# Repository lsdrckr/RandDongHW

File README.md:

# Stage chez Rang Dong

## Introduction

Dans le cadre de mon stage au Vietnam au Posts and Telecommunications Institute of Technologies, j'ai eu l'occasion de réaliser un projet avec une de leurs entreprise partenaire : Rand Dong. Cette entreprise est spécialisé dans la conception et la vente de matériel pour la domotique (smart home, smart cities...) tels que des lampes connectés, des hubs de capteurs (température, pression...) ou encore des caméras connectés. J'ai eu l'occasion de rejoindre 4 équipes :
- software : design d'application mobiles
- firmware : programmation de systèmes embarqués
- cloud : stockage dans des databases
- hardware : design de circuit imprimé
Mon choix s'est tourné vers le hardware, domaine dans lequel j'ai pu approfondir mes connaissances, et ce principalement d'un point de vue technique, grâce à l'équipe de Rang Dong qui m'a épaulé durant l'entièreté de mon stage.

## Projet

Le projet qui m'a été confié fût de réalisé un "Touch switch". Il s'agit d'interrupteurs tactiles permettant de contrôler, dans le cas de mon projet, 4 lampes. Voici ci-dessous une photo d'un produit commercialisé par Rand Dong sur lequel je vais me baser.

<center>
  <table>
    <tr>
      <td align="center">
        
        <br>
        <em>Touch Switch de chez Rang Dong</em>
      </td>
    </tr>
  </table>
</center>

A l'aide d'un contact avec le doigt sur l'un des ronds bleus, on allume une lampe à proximité. Ce principe à l'air simple car il est couramment utilisé et il nous accompagne au quotidien. Cependant, nous allons voir comment un tel projet est réalisé du début à la fin. Chez Rang Dong, ce genre d'objets est réalisé en 3 parties :
- une carte servant à l'alimentation (conversion AC/DC, relais...)
- une carte destiné au contrôle (microprocesseur...)
- le design de l'objet en lui-même, dans lequel sont camouflés les précédentes cartes
Dans un premier temps, j'ai conçu la carte servant à l'alimentation.

## Alimentation

### Choix des technologies

Le choix de l'alimentation est très importante pour tout projet, mais il l'est d'autant plus pour un projet comme celui-ci. En effet, ce dernier est destiné à n'importe quel client et de plus, ce client devra être en contact direct avec l'objet s'il souhaite l'utiliser. C'est pourquoi la sécurité était l'argument numéro un lors de mon choix. 2 propositions se sont vite dégagés au sein de l'équipe :
- alimentation buck
- alimentation flyback
D'un côté, l'alimentation buck permet la conversion à l'aide d'une inductance tandis que le flyback utilise un transformateur. De plus, le flyback permet une isolation galvanique entre la partie AC et la partie DC de la carte. Cependant, l'implémentation du flyback est plus compliqué que celle de l'alimentation buck. Comme dit précédemment, la sécurité de notre système est primordiale. Nous avons donc choisi l'alimentation flyback.

Nous avions besoin de récupérer 2 valeurs de tensions différents :
- une de 5V pour alimenter les relais
- une de 3.3V pour alimenter la carte de contrôle
Deux propositions sont égalements possible, dont voici les schémas équivalents :

<center>
  <table>
    <tr>
      <td align="center">
        
        <br>
        <em>Proposition 1 pour l'alim AC</em>
      </td>
      <td align="center">
        
        <br>
        <em>Proposition 2 pour l'alim AC</em>
      </td>
    </tr>
  </table>
</center>

Le premier choix consiste à utiliser 2 transformateurs ayant deux sorties et donc deux tensions de sortie différentes. Le deuxième, quant à lui, consiste à utiliser un régulateur de tension LDO pour récupérer 3.3V à partie des 5V de sortie du transformateur. Mon choix s’est naturellement posé sur le LDO, moins complexe à mettre en place et moins coûteux.
On mettra à l’entrée du transformateur un bloc snubber, permettant de limiter les pics de tension de l’alimentation AC et donc de protéger le transformateur.

### Choix des composants

Cette partie m’a énormément appris. Elle consiste non seulement à déterminer la valeurs des composants (résistances, capacités…) mais aussi à déterminer la taille des ses derniers en fonction de la puissance dissipée dans les résistances ou de la tension maximum des capacités. Pour les résistances, je me suis basé sur le tableau suivant venant de Fenghua.

<center>
  <table>
    <tr>
      <td align="center">
        
        <br>
        <em>Tableau de taille des résistances</em>
      </td>
    </tr>
  </table>
</center>

Pour les capacités, j’ai suivi le tableau de chez Kemet, qui donne la taille des composants en fonction de leurs valeurs et tension maximale.

<center>
  <table>
    <tr>
      <td align="center">
        
        <br>
        <em>Loi d'Ohm</em>
      </td>
    </tr>
  </table>
</center>

Pour mieux comprendre, voici un exemple rapide. Une résistance R est traversée par un courant I et a à ses bornes une tension V. La puissance qu’elle va dissiper est P = V\*I. En fonction de si l’on connaît seulement I ou V, on peut aussi déduire de la loi d'Ohm que P = V²/R ou P = I²\*R. Prenons dans notre exemple que nous avons déterminé R=1kΩ et Vmax=15V. On a alors P = 0,225W. En nous référant au tableau ci-dessus, on peut alors se permettre de choisir une résistance de taille 1206 ou plus, qui peut dissiper au maximum ¼W = 0,25W. Dans le cas où la puissance dépasse ½W, on peut mettre 2 résistances en parallèles, qui pourront dissiper 2 fois plus de puissance tout en gardant la même valeur. Prenons cette fois-ci Vmax=25V. On a alors P = 0,625W. En mettant deux résistances de 2kΩ en parallèle, on garde une résistance équivalente de 1kΩ et chacune d’entre elles doit seulement dissiper 0,3125W. Dans ce cas, on pourra choisir deux résistances de taille 2512.
Je n’ai pas détaillé le calcul pour chacun des composants, mais voici la méthode que j’ai suivie pour trouver leurs tailles.

### Implémentation sur Kicad

Maintenant que j’ai tous les éléments, je peux commencer à implémenter mon projet sur Kicad. J’ai séparé ce dernier en 4 grandes parties :

<center>
  <table>
    <tr>
      <td align="center">
        
        <br>
        <em>Alimentation AC</em>
      </td>
      <td align="center">
        
        <br>
        <em>Transformateur</em>
      </td>
    </tr>
    <tr>
      <td align="center">
        
        <br>
        <em>Driver flyback</em>
      </td>
      <td align="center">
        
        <br>
        <em>Relais</em>
      </td>
    </tr>
  </table>
</center>

J’ai également ajouté un connecteur 8 pins pour relier cette carte à celle de contrôle auquel seront connectés les sorties des 4 relais, la sortie du régulateur en 3.3V et la masse lui étant associée.
J’ai ensuite assigné chacun des éléments avec leurs empreintes, soit en choisissant les tailles définies précédemment, soit en demandant à mon équipe les datasheets qu’ils ont l’habitude d’utiliser pour les composants “spéciaux” tels que le driver, le transformateur, les relais…

## Bibliographie

[Page git du projet](https://github.com/lsdrckr/RangDongHW.git)

[Taille des résistances](https://www.fenghua.com/pdf/thickfilmchipres/thin_film_chipres.pdf)

[Taille des condensateurs](https://www.mouser.com/datasheet/2/447/KEM_A4005_ESH-3315849.pdf)

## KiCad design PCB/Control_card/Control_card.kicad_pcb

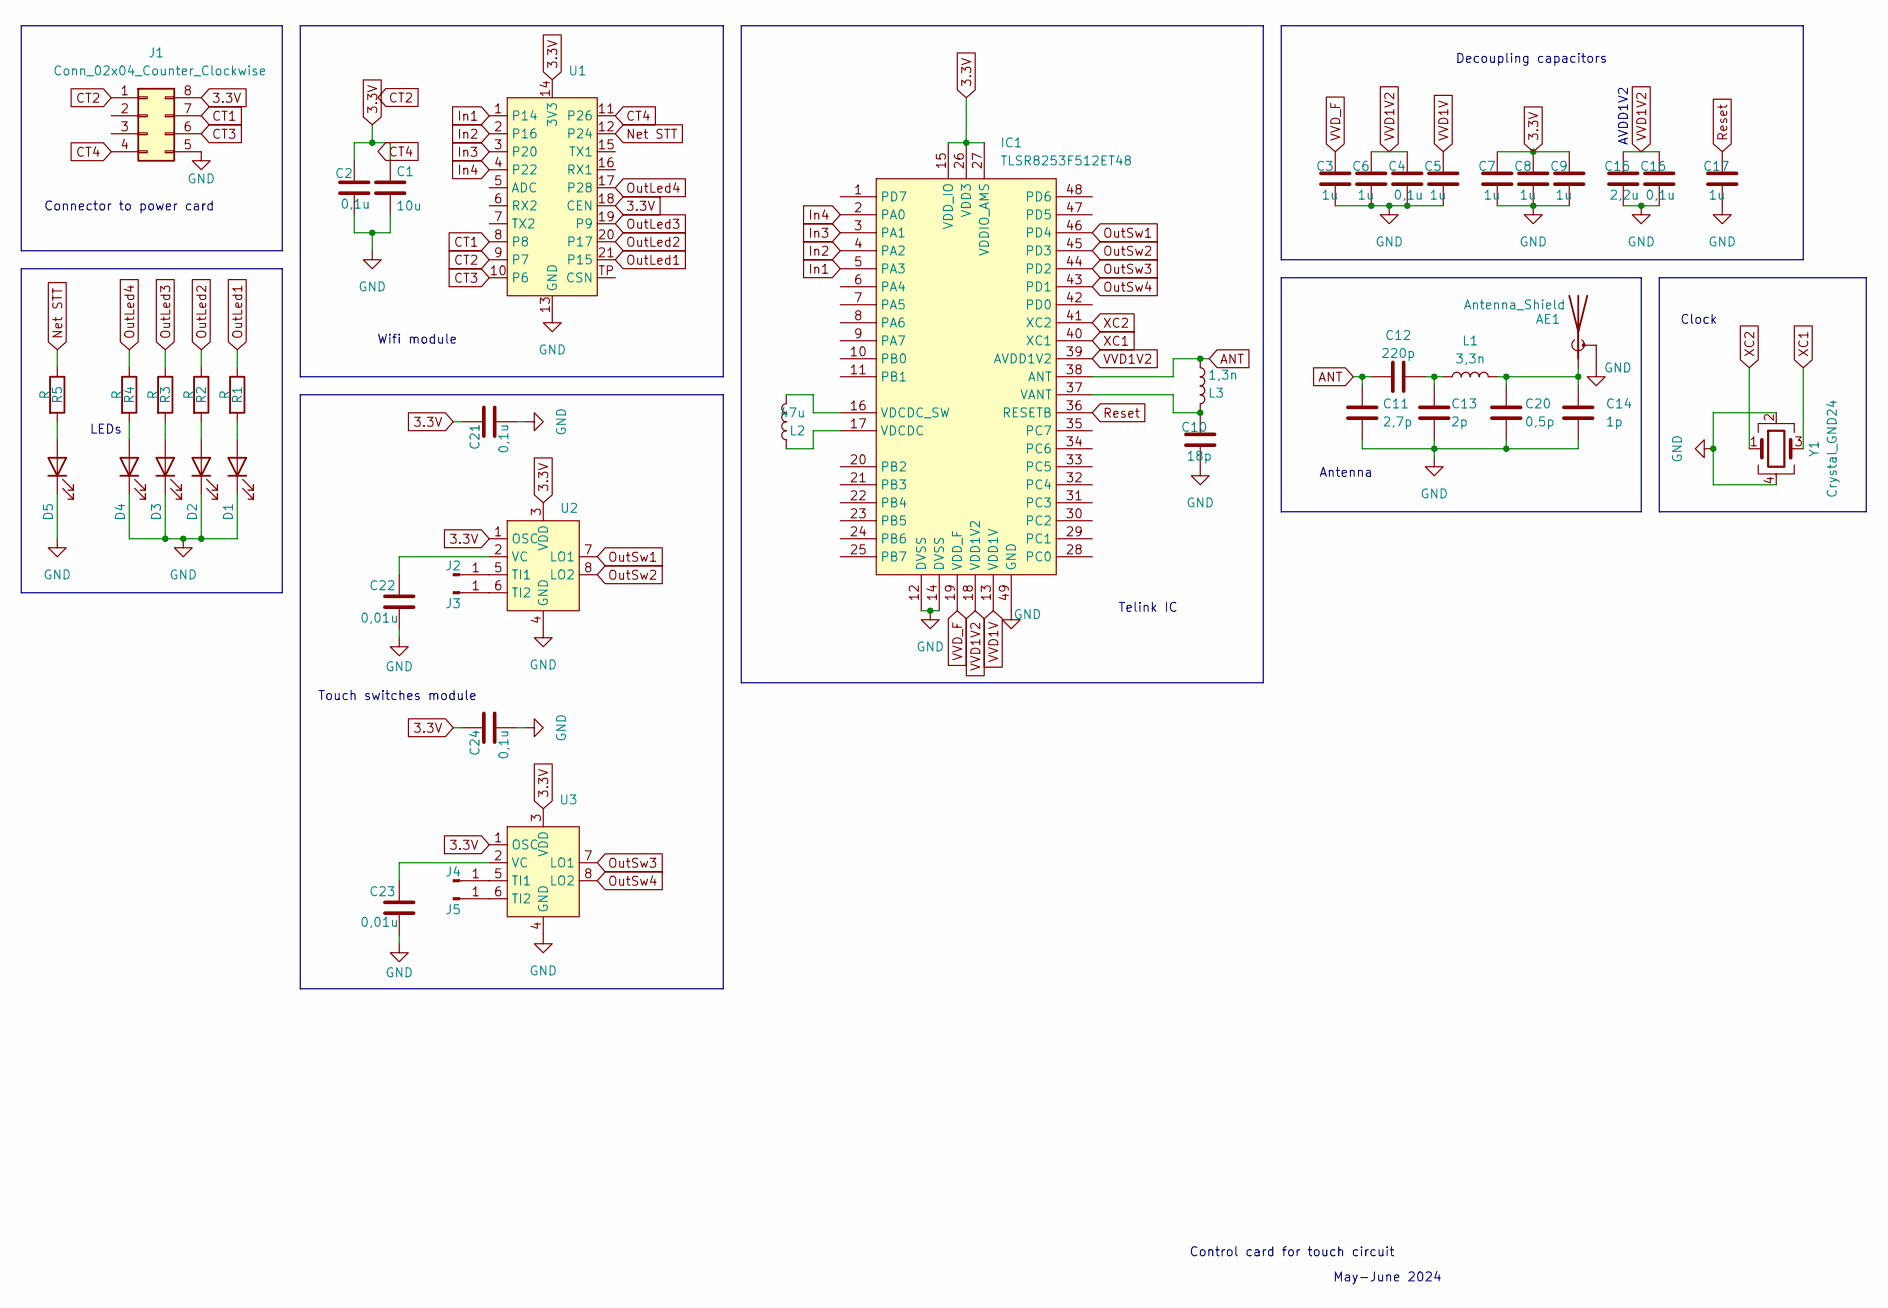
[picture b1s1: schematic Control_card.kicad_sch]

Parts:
AE1: Antenna_Shield; Antenna
C1: 10u; C_0603_1608Metric
C2, C4, C16, C21, C24: 0,1u; C_0603_1608Metric
C3, C5, C6, C7, C8, C9, C17: 1u; C_0603_1608Metric
C10: 18p; C_0603_1608Metric
C11: 2,7p; C_0603_1608Metric
C12: 220p; C_0603_1608Metric
C13: 2p; C_0603_1608Metric
C14: 1p; C_0603_1608Metric
C15: 2,2u; C_0603_1608Metric
C20: 0,5p; C_0603_1608Metric
C22, C23: 0,01u; C_0603_1608Metric
D1, D2, D3, D4, D5: LED; LED_0805_2012Metric
IC1: TLSR8253F512ET48; QFN-48-1EP_7x7mm_P0.5mm_EP5.6x5.6mm_ThermalVias; Mouser Part Number 141-TLSR8253F512ET32
J1: Conn_02x04_Counter_Clockwise; PinMale
J2, J3, J4, J5: Conn_01x01_Pin; TouchSwitch
L1: 3,3n; L_0603_1608Metric
L2: 47u; L_0805_2012Metric
L3: 1,3n; L_0603_1608Metric
R1, R2, R3, R4, R5: R; R_0603_1608Metric
U1: BK7231N
U2, U3: SOP-8_3.9x4.9mm_P1.27mm
Y1: Crystal_GND24; Crystal

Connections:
3.3V: C1.1, C2.1, C7.1, C8.1, C9.1, C21.1, C24.1, IC1.15 (VDD_IO), IC1.26 (VDD3), IC1.27 (VDDIO_AMS), J1.8, U1.14 (3V3), U1.18 (CEN), U2.1 (OSC), U2.3 (VDD), U3.1 (OSC), U3.3 (VDD)
ANT: C11.1, C12.1, IC1.38 (ANT), L3.2
CT1: J1.7, U1.8
CT2: J1.1, U1.9 (P7)
CT3: J1.6, U1.10 (P6)
CT4: J1.4, U1.11 (P26)
GND: AE1.2 (Shield), C1.2, C2.2, C3.2, C4.2, C5.2, C6.2, C7.2, C8.2, C9.2, C10.2, C11.2, C13.2, C14.2, C15.2, C16.2, C17.2, C20.2, C21.2, C22.2, C23.2, C24.2, D1.1 (K), D2.1 (K), D3.1 (K), D4.1 (K), D5.1 (K), IC1.12 (DVSS), IC1.14 (DVSS), IC1.49 (GND), J1.5, U1.13 (GND), U2.4 (GND), U3.4 (GND), Y1.2, Y1.4
In1: IC1.5 (PA3), U1.1 (P14)
In2: IC1.4 (PA2), U1.2 (P16)
In3: IC1.3 (PA1), U1.3 (P20)
In4: IC1.2 (PA0), U1.4 (P22)
Net STT: R5.1, U1.12 (P24)
unnamed: AE1.1 (A), C14.1, C20.1, L1.2
unnamed: C12.2, C13.1, L1.1
unnamed: D1.2 (A), R1.2
unnamed: D2.2 (A), R2.2
unnamed: D3.2 (A), R3.2
unnamed: D4.2 (A), R4.2
unnamed: D5.2 (A), R5.2
unnamed: C10.1, IC1.37 (VANT), L3.1
unnamed: IC1.17 (VDCDC), L2.1
unnamed: IC1.16 (VDCDC_SW), L2.2
unnamed: J2.1, U2.5 (TI1)
unnamed: J3.1, U2.6 (TI2)
unnamed: J4.1, U3.5 (TI1)
unnamed: J5.1, U3.6 (TI2)
unnamed: C22.1, U2.2 (VC)
unnamed: C23.1, U3.2 (VC)
OutLed1: R1.1, U1.21 (P15)
OutLed2: R2.1, U1.20 (P17)
OutLed3: R3.1, U1.19 (P9)
OutLed4: R4.1, U1.17 (P28)
OutSw1: IC1.46 (PD4), U2.7 (LO1)
OutSw2: IC1.45 (PD3), U2.8 (LO2)
OutSw3: IC1.44 (PD2), U3.7 (LO1)
OutSw4: IC1.43 (PD1), U3.8 (LO2)
Reset: C17.1, IC1.36 (RESETB)
VVD1V: C5.1, IC1.13 (VDD1V)
VVD1V2: C4.1, C6.1, C15.1, C16.1, IC1.18 (VDD1V2), IC1.39 (AVDD1V2)
VVD_F: C3.1, IC1.19 (VDD_F)
XC1: IC1.40 (XC1), Y1.3
XC2: IC1.41 (XC2), Y1.1

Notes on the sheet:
Connector to power card
Wifi module
LEDs
Decoupling capacitors
May-June 2024
Control card for touch circuit
Antenna
Telink IC
Touch switches module
Clock
AVDD1V2

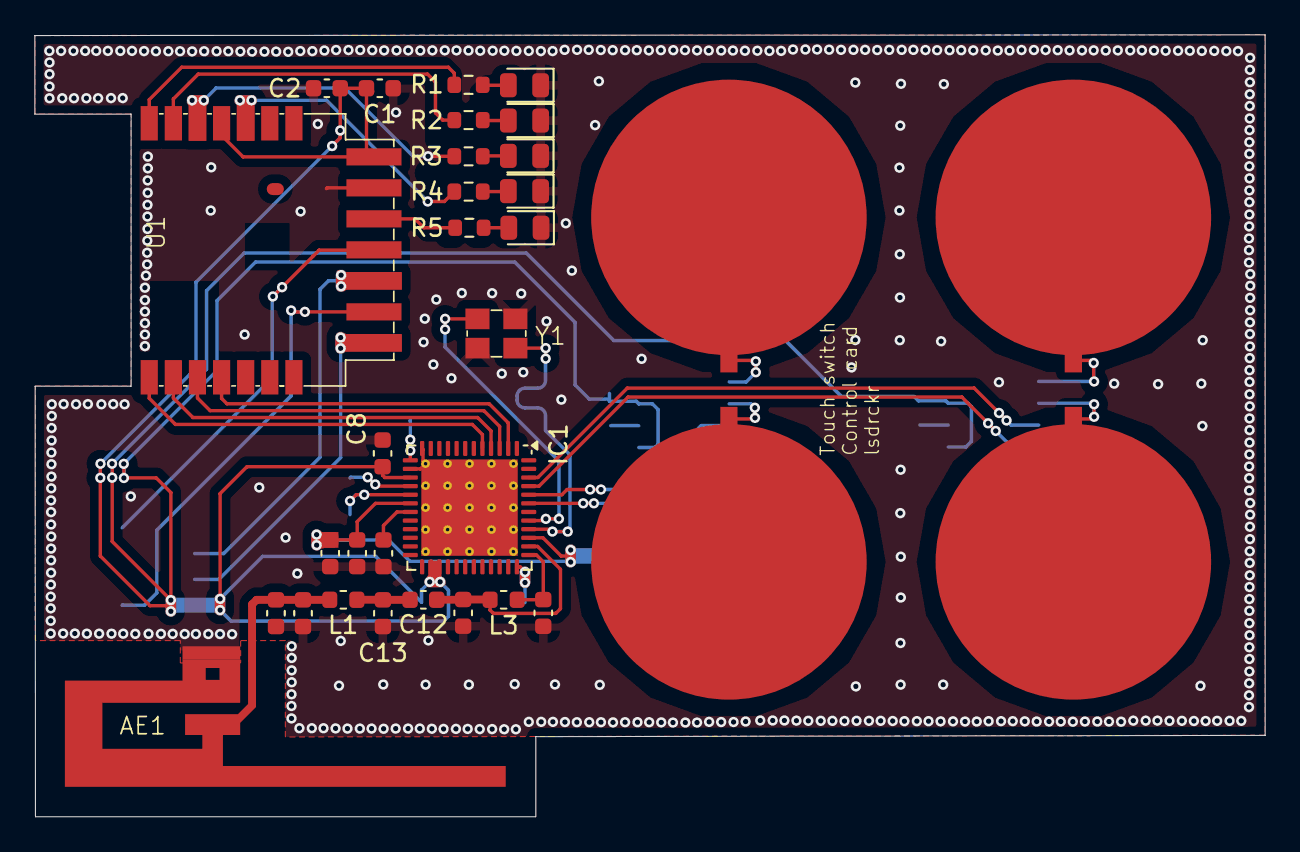
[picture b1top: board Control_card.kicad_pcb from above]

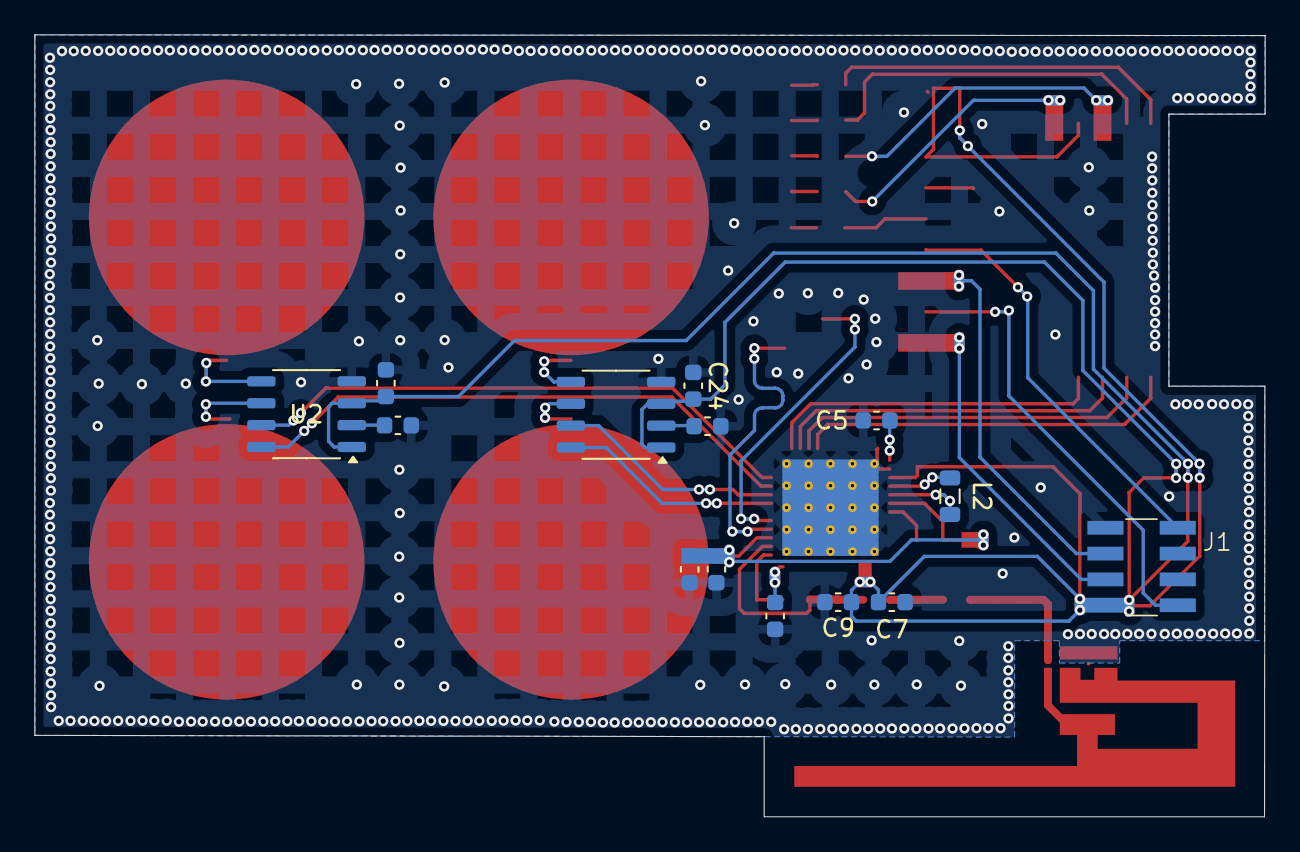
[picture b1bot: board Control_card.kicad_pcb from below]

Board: 2 copper layers, 71.4 x 45.4 mm, 46 parts (14 on the bottom side), 42 nets.

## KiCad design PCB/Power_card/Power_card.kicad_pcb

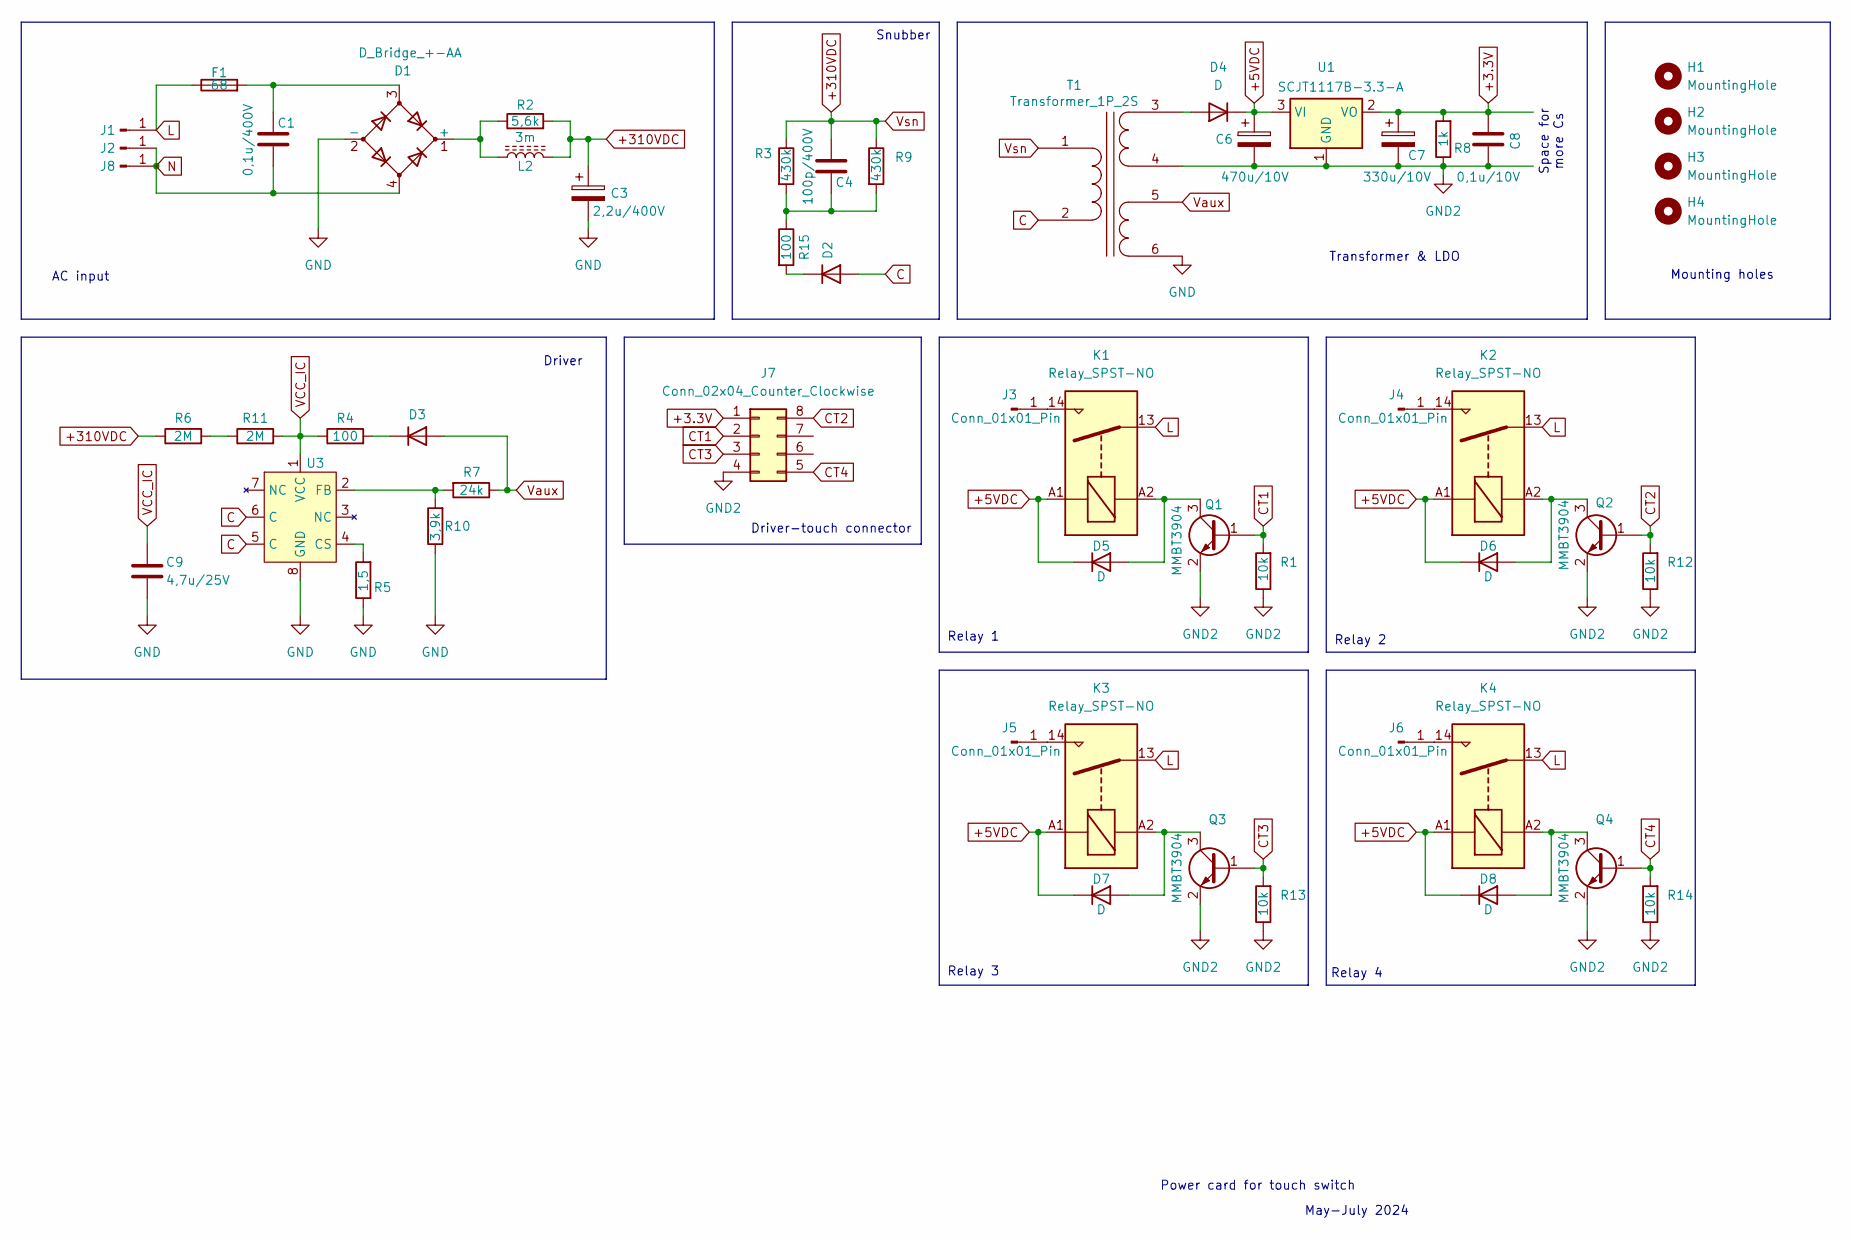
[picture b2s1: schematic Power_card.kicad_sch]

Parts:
C1: 0,1u/400V; MKP-X2-100NR10
C3: 2,2u/400V; CP_Radial_D8.0mm_P3.50mm
C4: 100p/400V; C_1206_3216Metric
C6: 470u/10V; CP_Radial_D8.0mm_P3.50mm
C7: 330u/10V; CP_Radial_D8.0mm_P3.50mm
C8: 0,1u/10V; C_0805_2012Metric
C9: 4,7u/25V; C_0805_2012Metric
D1: D_Bridge_+-AA; Diode_Bridge_Diotec_ABS
D2, D3, D4: D; D_SMA
D5, D6, D7, D8: D; D_SOD-123
F1: 68; Fuse
H1, H2, H3, H4: MountingHole; MountingHole_2.2mm_M2_Pad_Via
J1, J2, J3, J4, J5, J6, J8: Conn_01x01_Pin; AC_pad
J7: Conn_02x04_Counter_Clockwise; PinFemelle
K1, K2, K3, K4: Relay_SPST-NO; relay
L2: 3m; L_Radial_D7.5mm_P3.50mm_Fastron_07P
Q1, Q2, Q3, Q4: MMBT3904; SOT-23
R1, R12, R13, R14: 10k; R_0805_2012Metric
R2: 5,6k; R_1206_3216Metric
R3, R9: 430k; R_1206_3216Metric
R4: 100; R_0805_2012Metric
R5: 1,5; R_1206_3216Metric
R6, R11: 2M; R_1206_3216Metric
R7: 24k; R_1206_3216Metric
R8: 1k; R_0805_2012Metric
R10: 3,9k; R_1206_3216Metric
R15: 100; R_1206_3216Metric
T1: Transformer_1P_2S; Transformer_V2_1
U1: SCJT1117B-3.3-A; SOT-223-3_TabPin2
U3: SOP-8_3.9x4.9mm_P1.27mm

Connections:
+3.3V: C7.1, C8.2, J7.1, R8.2, U1.2 (VO)
+5VDC: C6.1, D4.1 (K), D5.1 (K), D6.1 (K), D7.1 (K), D8.1 (K), K1.A1, K2.A1, K3.A1, K4.A1, U1.3 (VI)
+310VDC: C3.1, C4.1, L2.2, R2.2, R3.1, R6.1, R9.1, T1.1 (AA)
C: D2.2 (A), T1.2 (AB), U3.5 (C), U3.6 (C)
CT1: J7.2, Q1.1 (B), R1.2
CT2: J7.8, Q2.1 (B), R12.2
CT3: J7.3, Q3.1 (B), R13.2
CT4: J7.5, Q4.1 (B), R14.2
GND: C3.2, C9.2, D1.2 (-), R5.1, R10.1, T1.6 (SD), U3.8 (GND)
GND2: C6.2, C7.2, C8.1, J7.4, Q1.2 (E), Q2.2 (E), Q3.2 (E), Q4.2 (E), R1.1, R8.1, R12.1, R13.1, R14.1, T1.4 (SB), U1.1 (GND)
L: F1.1, J1.1, K1.13, K2.13, K3.13, K4.13
N: C1.2, D1.4, J2.1, J8.1
unnamed: C1.1, D1.3, F1.2
unnamed: C4.2, R3.2, R9.2, R15.1
unnamed: D1.1 (+), L2.1, R2.1
unnamed: D2.1 (K), R15.2
unnamed: D3.1 (K), R4.2
unnamed: D4.2 (A), T1.3 (SA)
unnamed: D5.2 (A), K1.A2, Q1.3 (C)
unnamed: D6.2 (A), K2.A2, Q2.3 (C)
unnamed: D7.2 (A), K3.A2, Q3.3 (C)
unnamed: D8.2 (A), K4.A2, Q4.3 (C)
unnamed: J3.1, K1.14
unnamed: J4.1, K2.14
unnamed: J5.1, K3.14
unnamed: J6.1, K4.14
unnamed: R6.2, R11.1
unnamed: R5.2, U3.4 (CS)
unnamed: R7.2, R10.2, U3.2 (FB)
VCC_IC: C9.1, R4.1, R11.2, U3.1 (VCC)
Vaux: D3.2 (A), R7.1, T1.5 (SC)

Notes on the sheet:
Relay 2
Power card for touch switch
Relay 1
AC input
May-July 2024
Relay 4
Space for more Cs
Driver-touch connector
Snubber
Relay 3
Driver
Mounting holes
Transformer & LDO

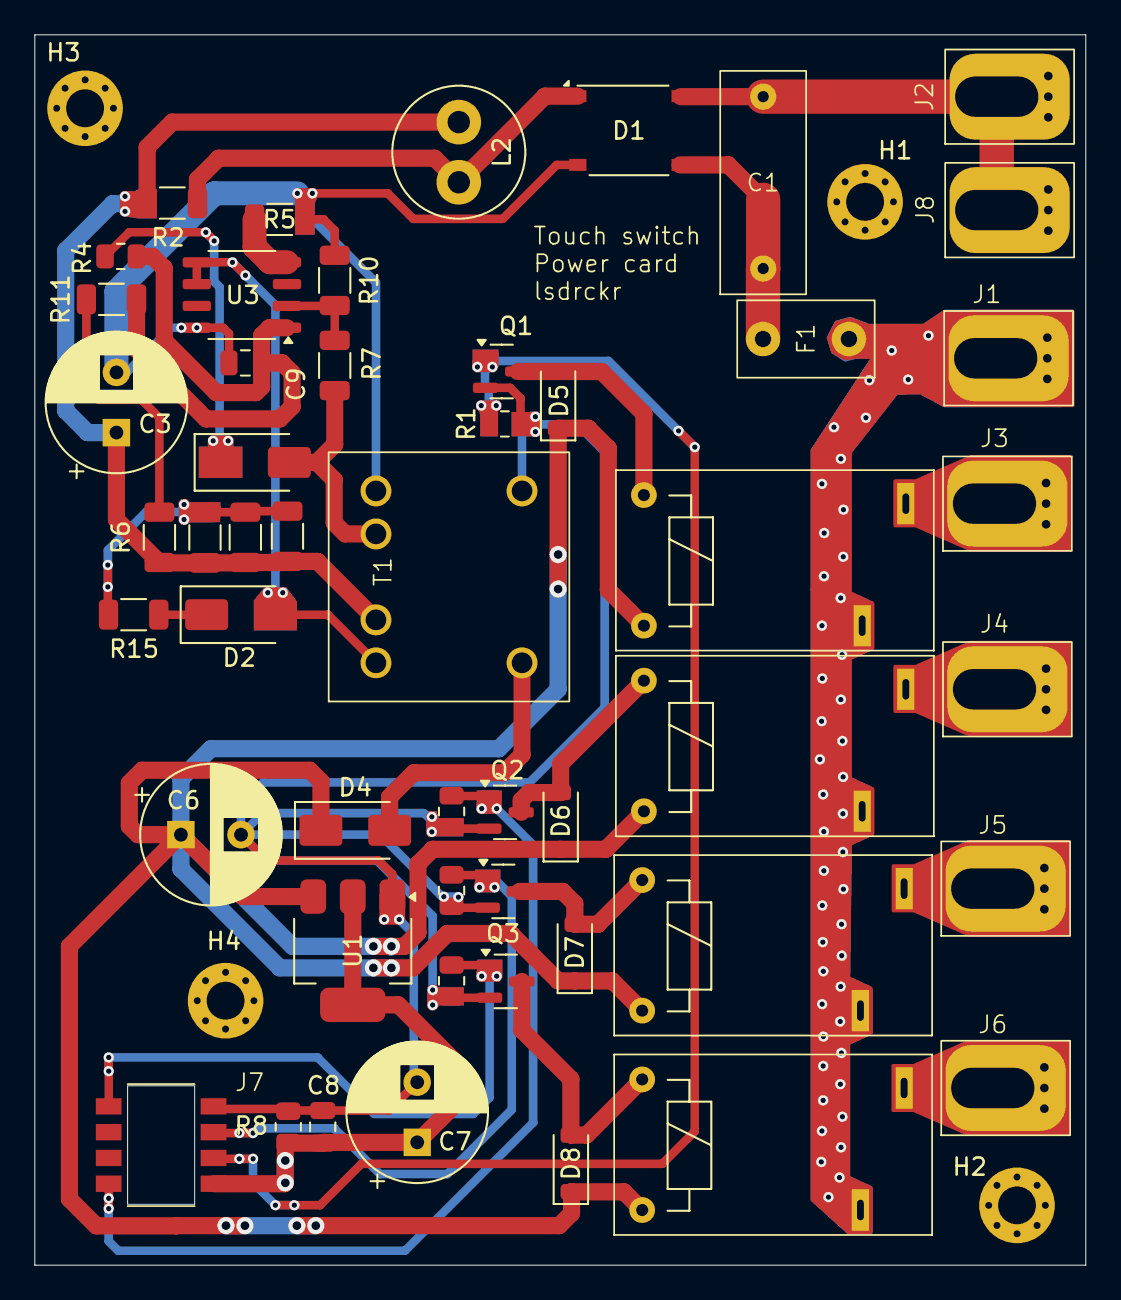
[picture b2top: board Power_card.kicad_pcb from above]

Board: 2 copper layers, 61.2 x 71.6 mm, 55 parts (0 on the bottom side), 31 nets.

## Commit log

2024-05-13 Touch switch test
2024-05-14 Début bloc AC et Flyback/LDO
2024-05-16 Snubber
2024-05-16 Début schematic
2024-05-16 Assignation footprints
2024-05-17 Ajout .gitignore
2024-05-17 Début routage
2024-05-17 Routage : regroupement des blocs
2024-05-20 Routage compact
2024-05-20 Routage compact & génération gerber
2024-05-20 Correction footprint relais
2024-05-20 Correction footprints relais et transfo
2024-05-20 Ajout mounting holes
2024-05-21 Ajout pads AC & modifs pistes
2024-05-21 Ajout README
2024-05-21 Regroupement partie AC
2024-05-21 J7 femelle
2024-05-21 Rédaction README
2024-05-21 Routage : séparation primaire/secondaire
2024-05-21 Routage
2024-05-22 Génération gerber
2024-05-23 Modif footprint relais & refaçonnage
2024-05-24 Modif vias
2024-05-27 Projet renommé
2024-05-27 Ajout carte de contrôle
2024-05-27 Début carte contrôle
2024-05-27 Ajout crystal
2024-05-28 Continuation routage & ajout antenne
2024-05-29 Finalisation carte contrôle
2024-05-29 Ajout des touch switch
2024-05-30 Changement de connecteurs
2024-05-30 Ajout des footprints
2024-05-31 Rota IC contrôle
2024-06-11 Ajout firmware
